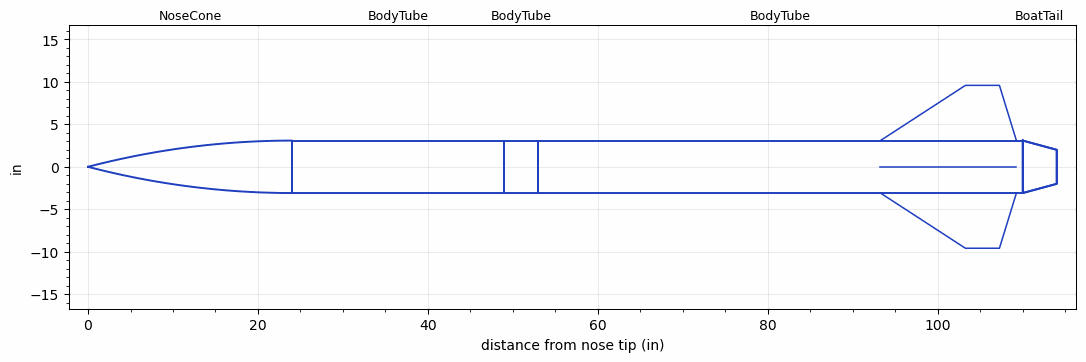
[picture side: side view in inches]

<RASAeroDocument>
 <FileVersion>2</FileVersion>
 <RocketDesign>
  <NoseCone>
   <Length>24</Length>
   <Diameter>6.17</Diameter>
   <Shape>Tangent Ogive</Shape>
   <Location>0</Location>
  </NoseCone>
  <BodyTube>
   <Length>24.9999</Length>
   <Diameter>6.17</Diameter>
   <Location>24</Location>
  </BodyTube>
  <BodyTube>
   <Length>4</Length>
   <Diameter>6.17</Diameter>
   <Location>48.9999</Location>
  </BodyTube>
  <BodyTube>
   <Length>56.9999</Length>
   <Diameter>6.17</Diameter>
   <RailGuideDiameter>0.49</RailGuideDiameter>
   <RailGuideHeight>0.56</RailGuideHeight>
   <Location>52.9999</Location>
   <BoattailLength>4</BoattailLength>
   <BoattailRearDiameter>4</BoattailRearDiameter>
   <Fin>
    <Count>4</Count>
    <Chord>16</Chord>
    <Span>6.5</Span>
    <SweepDistance>10</SweepDistance>
    <TipChord>4</TipChord>
    <Thickness>0.1875</Thickness>
    <Location>16.75</Location>
    <AirfoilSection>Rounded</AirfoilSection>
   </Fin>
  </BodyTube>
  <BoatTail>
   <Length>4</Length>
   <Diameter>6.17</Diameter>
   <RearDiameter>4</RearDiameter>
   <Location>109.9998</Location>
  </BoatTail>
  <Surface>Camouflage Paint</Surface>
  <ModifiedBarrowman>False</ModifiedBarrowman>
  <Turbulence>False</Turbulence>
  <UseBooster1>False</UseBooster1>
  <UseBooster2>False</UseBooster2>
 </RocketDesign>
 <LaunchSite>
  <Altitude>2920</Altitude>
  <Pressure>26.9</Pressure>
  <RodAngle>4</RodAngle>
  <RodLength>15.42</RodLength>
  <Temperature>90</Temperature>
  <WindSpeed>4.48</WindSpeed>
 </LaunchSite>
 <Recovery>
  <Altitude1>656.168</Altitude1>
  <Altitude2>1000</Altitude2>
  <DeviceType1>Parachute</DeviceType1>
  <DeviceType2>Parachute</DeviceType2>
  <Event1>True</Event1>
  <Event2>True</Event2>
  <Size1>35.9999</Size1>
  <Size2>167.9997</Size2>
  <EventType1>Apogee</EventType1>
  <EventType2>Altitude</EventType2>
  <CD1>0.97</CD1>
  <CD2>0</CD2>
 </Recovery>
 <SimulationList>
  <Simulation>
   <SustainerEngine>M2000R  (AT)</SustainerEngine>
   <SustainerLaunchWt>58.5057</SustainerLaunchWt>
   <SustainerCG>69.8589</SustainerCG>
   <SustainerIgnitionDelay>0</SustainerIgnitionDelay>
   <Booster1SeparationDelay>0</Booster1SeparationDelay>
   <Booster1IgnitionDelay>0</Booster1IgnitionDelay>
   <IncludeBooster1>False</IncludeBooster1>
   <Booster2Delay>0</Booster2Delay>
   <IncludeBooster2>False</IncludeBooster2>
   <TimetoApogee>28.51056</TimetoApogee>
   <MaxAltitude>12993.87</MaxAltitude>
   <MaxVelocity>1045.05</MaxVelocity>
  </Simulation>
  <Simulation>
   <SustainerEngine>M2500T  (AT)</SustainerEngine>
   <SustainerLaunchWt>56.4711</SustainerLaunchWt>
   <SustainerCG>68.814</SustainerCG>
   <SustainerIgnitionDelay>0</SustainerIgnitionDelay>
   <Booster1SeparationDelay>0</Booster1SeparationDelay>
   <Booster1IgnitionDelay>0</Booster1IgnitionDelay>
   <IncludeBooster1>False</IncludeBooster1>
   <Booster2Delay>0</Booster2Delay>
   <IncludeBooster2>False</IncludeBooster2>
   <TimetoApogee>28.79056</TimetoApogee>
   <MaxAltitude>13883.93</MaxAltitude>
   <MaxVelocity>1131.953</MaxVelocity>
  </Simulation>
  <Simulation>
   <SustainerEngine>M1939W  (AT)</SustainerEngine>
   <SustainerLaunchWt>58.5086</SustainerLaunchWt>
   <SustainerCG>69.8602</SustainerCG>
   <SustainerIgnitionDelay>0</SustainerIgnitionDelay>
   <Booster1SeparationDelay>0</Booster1SeparationDelay>
   <Booster1IgnitionDelay>0</Booster1IgnitionDelay>
   <IncludeBooster1>False</IncludeBooster1>
   <Booster2Delay>0</Booster2Delay>
   <IncludeBooster2>False</IncludeBooster2>
  </Simulation>
  <Simulation>
   <SustainerEngine>M750W  (AT)</SustainerEngine>
   <SustainerLaunchWt>58.0407</SustainerLaunchWt>
   <SustainerCG>69.6528</SustainerCG>
   <SustainerIgnitionDelay>0</SustainerIgnitionDelay>
   <Booster1SeparationDelay>0</Booster1SeparationDelay>
   <Booster1IgnitionDelay>0</Booster1IgnitionDelay>
   <IncludeBooster1>False</IncludeBooster1>
   <Booster2Delay>0</Booster2Delay>
   <IncludeBooster2>False</IncludeBooster2>
  </Simulation>
  <Simulation>
   <SustainerEngine>M2400T  (AT)</SustainerEngine>
   <SustainerLaunchWt>52.9154</SustainerLaunchWt>
   <SustainerCG>67.8548</SustainerCG>
   <SustainerIgnitionDelay>0</SustainerIgnitionDelay>
   <Booster1SeparationDelay>0</Booster1SeparationDelay>
   <Booster1IgnitionDelay>0</Booster1IgnitionDelay>
   <IncludeBooster1>False</IncludeBooster1>
   <Booster2Delay>0</Booster2Delay>
   <IncludeBooster2>False</IncludeBooster2>
  </Simulation>
  <Simulation>
   <SustainerLaunchWt>53.4243</SustainerLaunchWt>
   <SustainerCG>68.1442</SustainerCG>
   <SustainerIgnitionDelay>0</SustainerIgnitionDelay>
   <Booster1SeparationDelay>0</Booster1SeparationDelay>
   <Booster1IgnitionDelay>0</Booster1IgnitionDelay>
   <IncludeBooster1>False</IncludeBooster1>
   <Booster2Delay>0</Booster2Delay>
   <IncludeBooster2>False</IncludeBooster2>
  </Simulation>
 </SimulationList>
</RASAeroDocument>
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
